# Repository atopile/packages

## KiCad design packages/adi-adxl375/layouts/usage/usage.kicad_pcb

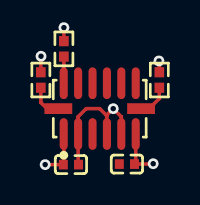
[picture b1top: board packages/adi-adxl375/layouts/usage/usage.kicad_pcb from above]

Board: 2 copper layers, 6 parts (0 on the bottom side), 6 nets.

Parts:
C1, C2: 0F; C0402
R1: 10000Ω; R0402
R2, R3: 4700Ω; R0402
U1: LGA-14_L5.0-W3.0-P0.80-BL

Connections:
RESERVED: U1.3, U1.11
SCL: R2.1, U1.14
SDA: R3.1, U1.13
hv: C1.1, C2.1, R1.2, R2.2, R3.2, U1.1, U1.6, U1.12
lv: C1.2, C2.2, U1.2, U1.4, U1.5
nCS: R1.1, U1.7

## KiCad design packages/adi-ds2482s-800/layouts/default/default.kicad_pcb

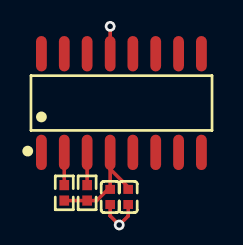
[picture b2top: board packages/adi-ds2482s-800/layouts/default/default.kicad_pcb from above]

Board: 2 copper layers, 5 parts (0 on the bottom side), 4 nets.

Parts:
C1, C2: 1±20.0%F; C0402
R1, R2: 10000±5.0%Ω; R0402
U1: SOIC-16_L9.9-W3.9-P1.27-LS6.0-BL

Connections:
SCL: R1.2, U1.2
SDA: R2.2, U1.3
hv: C1.1, C2.1, R1.1, R2.1, U1.4
lv: C1.2, C2.2, U1.6, U1.7, U1.8, U1.13

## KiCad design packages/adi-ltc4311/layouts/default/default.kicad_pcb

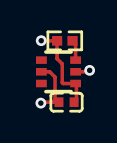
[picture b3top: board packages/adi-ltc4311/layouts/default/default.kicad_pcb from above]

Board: 2 copper layers, 3 parts (0 on the bottom side), 3 nets.

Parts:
C1: 1.0000000000000001e-07F; C0402
R1: 10000.0Ω; R0402
U1: SC-70-6_L2.1-W1.3-P0.65-LS2.1-BR

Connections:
ENABLE: R1.2, U1.3
hv: C1.1, R1.1, U1.1
lv: C1.2, U1.2, U1.5

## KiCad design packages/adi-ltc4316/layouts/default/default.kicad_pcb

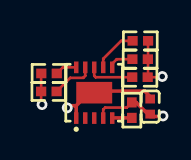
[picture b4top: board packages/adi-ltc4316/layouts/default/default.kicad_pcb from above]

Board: 2 copper layers, 8 parts (0 on the bottom side), 8 nets.

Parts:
C1: 1±20.0%F; C0402
R1, R2, R3, R4, R5, R6: 10000±5.0%Ω; R0402
U1: DFN-10_L3.0-W3.0-P0.50-BL-EP

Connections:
ENABLE: R6.1, U1.5
READY: R5.1, U1.6
SCL: R1.1, U1.10
SDA: R2.1, U1.7
hv: C1.1, R1.2, R2.2, R3.2, R4.2, R5.2, R6.2, U1.4
i2c_out-SCL: R3.1, U1.9
i2c_out-SDA: R4.1, U1.8
lv: C1.2, U1.1, U1.11

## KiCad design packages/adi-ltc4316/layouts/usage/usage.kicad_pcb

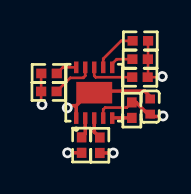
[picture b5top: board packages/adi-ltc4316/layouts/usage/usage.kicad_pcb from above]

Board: 2 copper layers, 10 parts (0 on the bottom side), 10 nets.

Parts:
C1: 1.0000000000000001e-07F; C0402
R2, R3, R4, R5, R6, R7, R8, R9: 10000.0Ω; R0402
U1: DFN-10_L3.0-W3.0-P0.50-BL-EP

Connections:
ENABLE: R9.1, U1.5
READY: R8.1, U1.6
SCL: R4.1, U1.10
SDA: R5.1, U1.7
XORH: R2.1, U1.2
XORL: R3.1, U1.3
hv: C1.1, R2.2, R4.2, R5.2, R6.2, R7.2, R8.2, R9.2, U1.4
i2c_out-SCL: R6.1, U1.9
i2c_out-SDA: R7.1, U1.8
lv: C1.2, R3.2, U1.1, U1.11
